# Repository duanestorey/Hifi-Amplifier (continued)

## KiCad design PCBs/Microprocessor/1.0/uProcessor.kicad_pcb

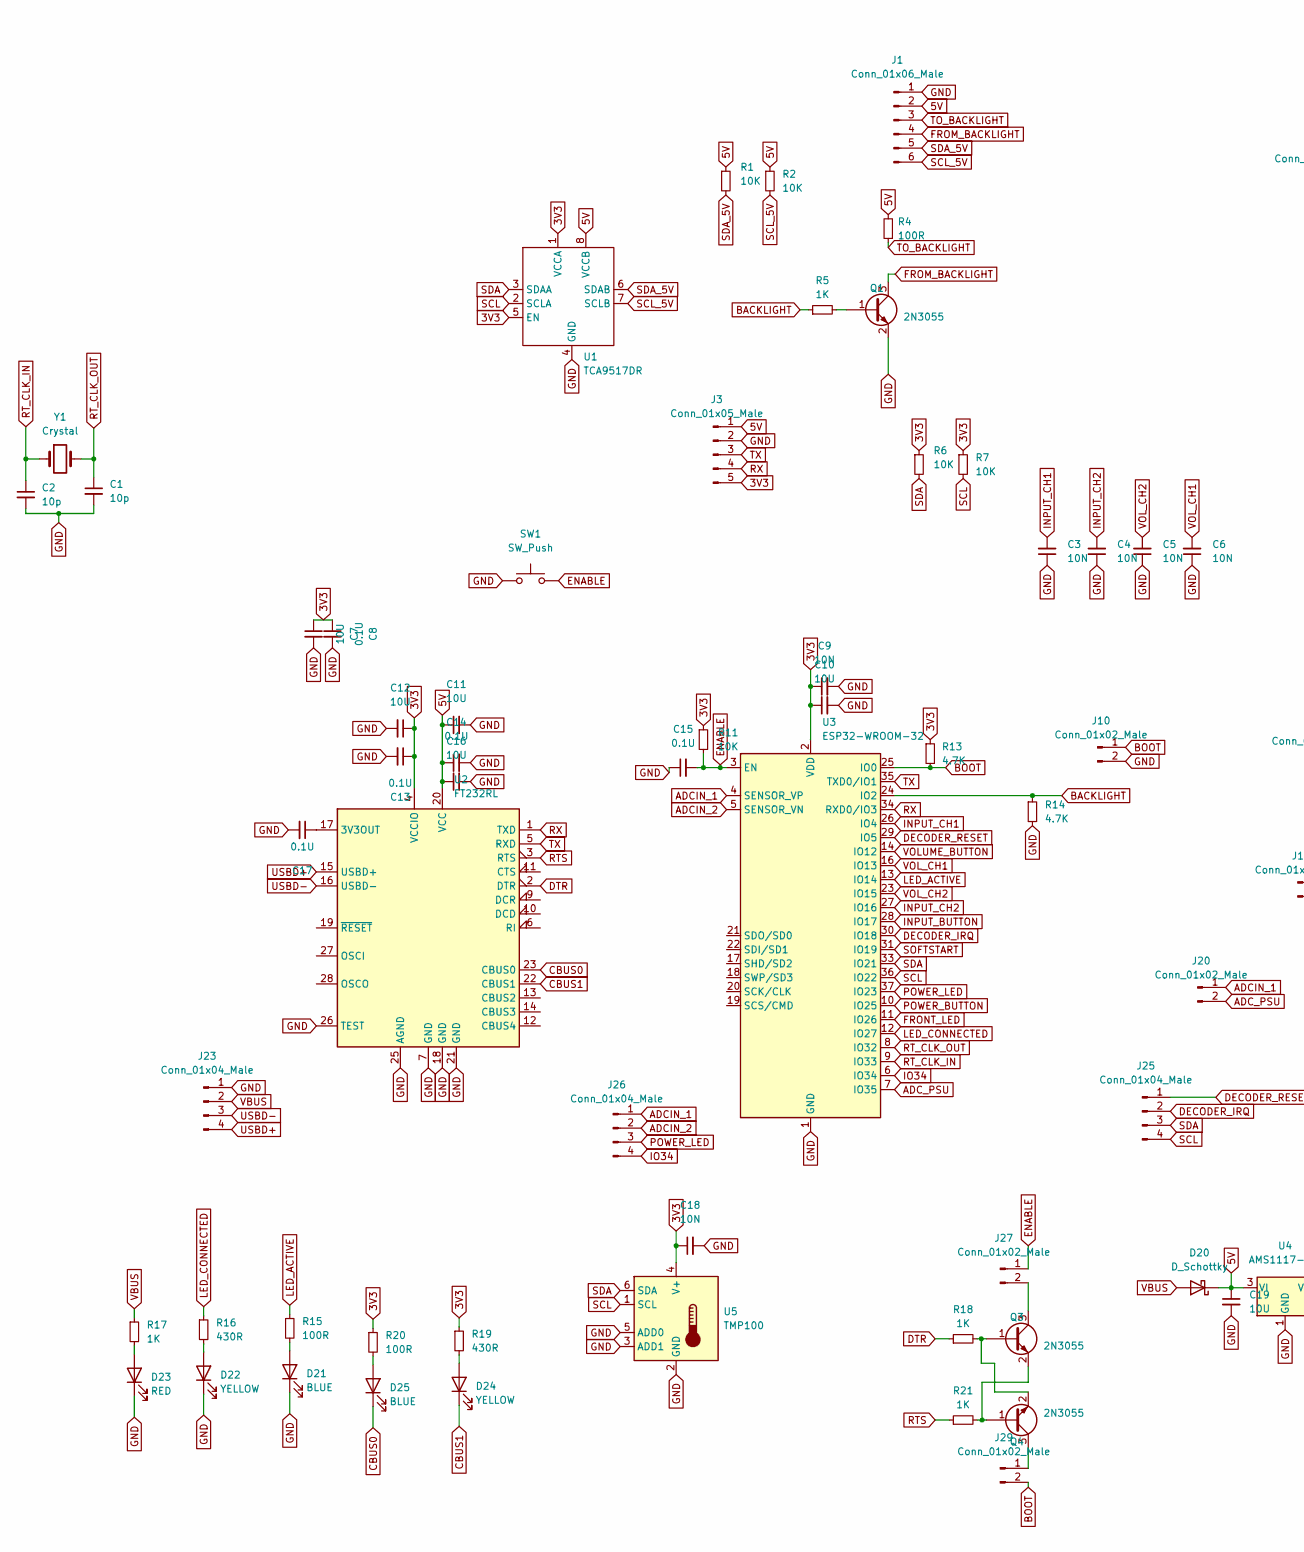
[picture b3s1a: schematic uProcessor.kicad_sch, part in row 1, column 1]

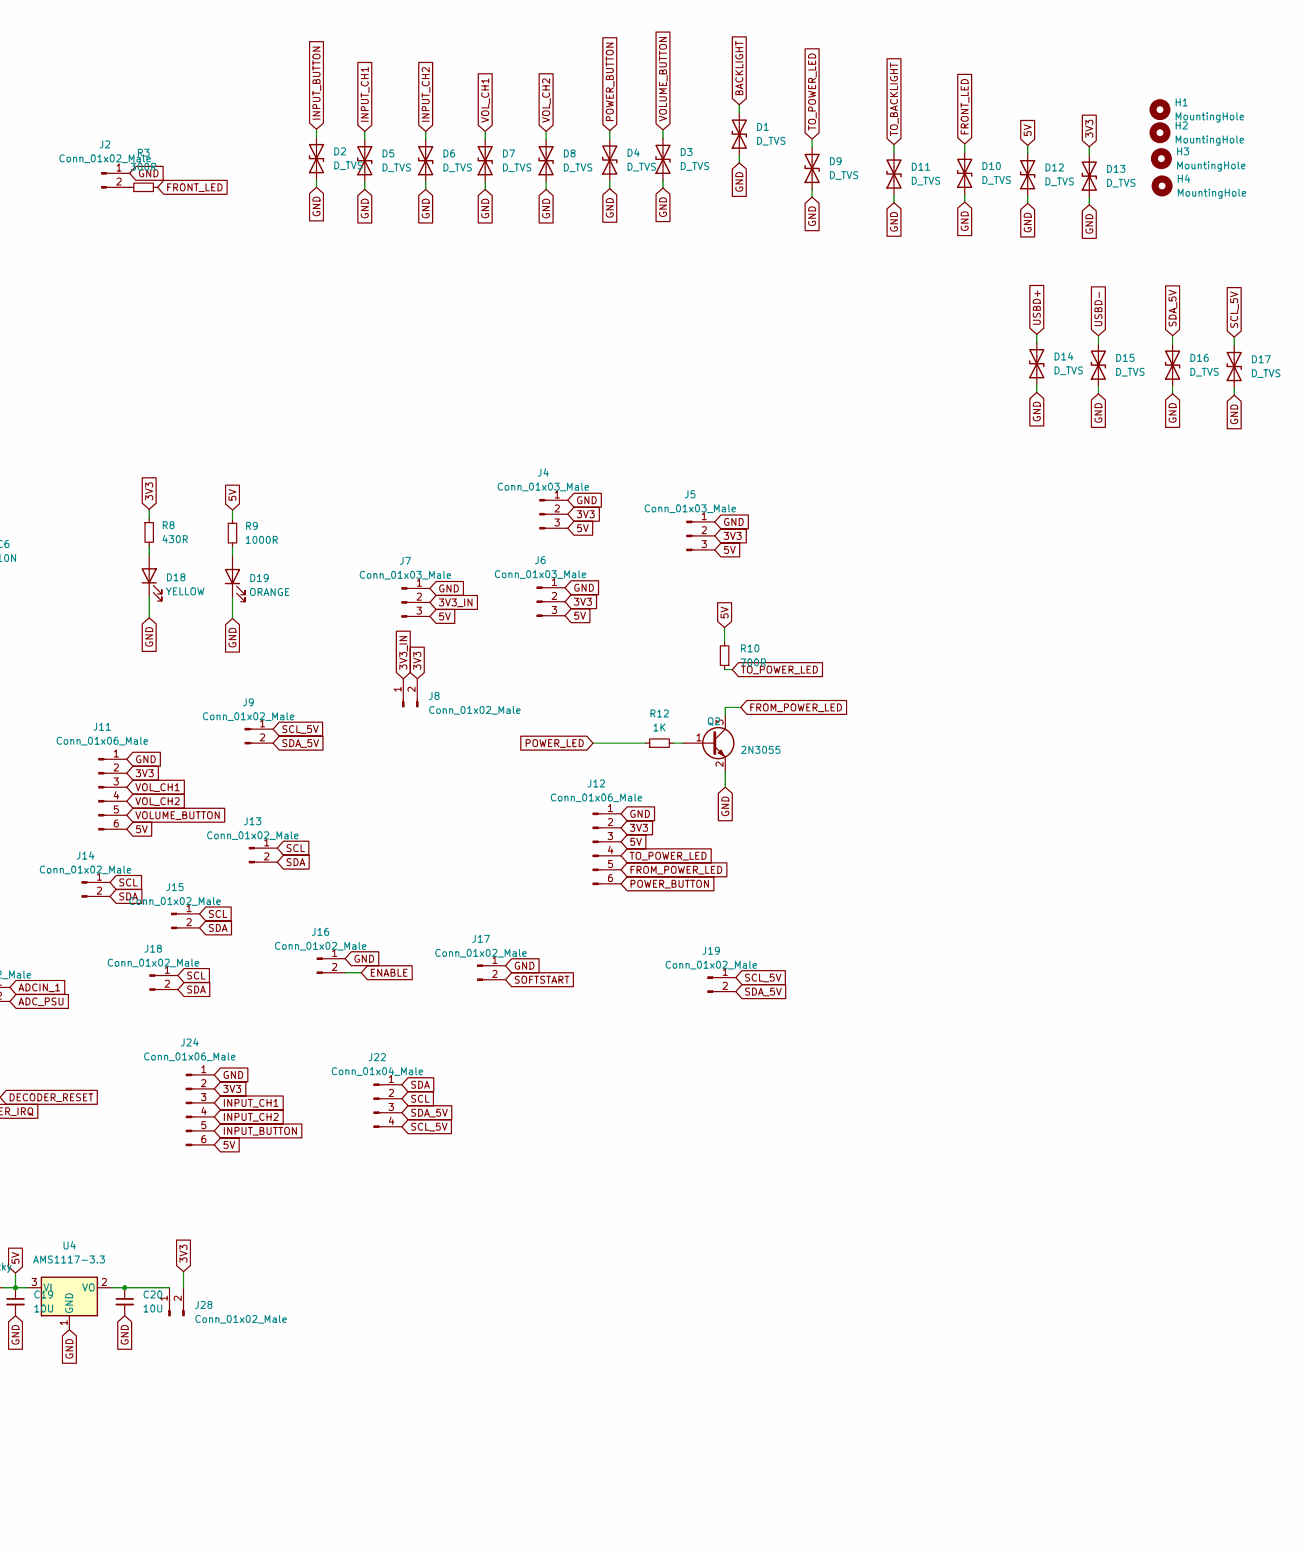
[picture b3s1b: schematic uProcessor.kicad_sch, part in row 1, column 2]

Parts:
C1, C2: 10p; C_0603_1608Metric_Pad1.08x0.95mm_HandSolder
C3, C4, C5, C6: 10N; C_0603_1608Metric_Pad1.08x0.95mm_HandSolder
C7, C10, C11, C12, C16, C19, C20: 10U; C_1206_3216Metric_Pad1.33x1.80mm_HandSolder
C8, C13, C14, C15, C17: 0.1U; C_0805_2012Metric_Pad1.18x1.45mm_HandSolder
C9, C18: 10N; C_0805_2012Metric_Pad1.18x1.45mm_HandSolder
D1, D2, D3, D4, D5, D6, D7, D8, D9, D10, D11, D12, D13, D14, D15, D16, D17: D_TVS; D_SOD-523
D18: YELLOW; LED_0805_2012Metric_Pad1.15x1.40mm_HandSolder; LCSC NCD0603R1
D19: ORANGE; LED_0805_2012Metric_Pad1.15x1.40mm_HandSolder; LCSC XL-1608UBC-04
D20: D_Schottky; D_SMA_Handsoldering
D21, D25: BLUE; LED_0805_2012Metric_Pad1.15x1.40mm_HandSolder; LCSC XL-1608UBC-04
D22, D24: YELLOW; LED_0805_2012Metric_Pad1.15x1.40mm_HandSolder; LCSC XL-1608UBC-04
D23: RED; LED_0805_2012Metric_Pad1.15x1.40mm_HandSolder; LCSC XL-1608UBC-04
H1, H2, H3, H4: MountingHole; MountingHole_3.2mm_M3
J1, J11, J12, J24: Conn_01x06_Male; JST_PH_B6B-PH-K_1x06_P2.00mm_Vertical
J2, J9, J13, J14, J15, J16, J17, J18, J19, J20: Conn_01x02_Male; JST_PH_B2B-PH-K_1x02_P2.00mm_Vertical
J3: Conn_01x05_Male; PinSocket_1x05_P2.54mm_Vertical
J4, J6: Conn_01x03_Male; PinHeader_1x03_P2.54mm_Vertical
J5, J7: Conn_01x03_Male; JST_PH_B3B-PH-K_1x03_P2.00mm_Vertical
J8, J10, J27, J28, J29: Conn_01x02_Male; PinHeader_1x02_P2.54mm_Vertical
J22, J26: Conn_01x04_Male; PinHeader_1x04_P2.54mm_Vertical
J23, J25: Conn_01x04_Male; JST_PH_B4B-PH-K_1x04_P2.00mm_Vertical
Q1, Q2, Q3, Q4: 2N3055; TSOT-23
R1, R2, R6, R7, R11: 10K; R_0603_1608Metric_Pad0.98x0.95mm_HandSolder
R3: 300R; R_0603_1608Metric_Pad0.98x0.95mm_HandSolder
R4, R15, R20: 100R; R_0603_1608Metric_Pad0.98x0.95mm_HandSolder
R5, R12, R17, R18, R21: 1K; R_0603_1608Metric_Pad0.98x0.95mm_HandSolder
R8, R16, R19: 430R; R_0603_1608Metric_Pad0.98x0.95mm_HandSolder
R9: 1000R; R_0603_1608Metric_Pad0.98x0.95mm_HandSolder
R10: 700R; R_0603_1608Metric_Pad0.98x0.95mm_HandSolder
R13, R14: 4.7K; R_0603_1608Metric_Pad0.98x0.95mm_HandSolder
SW1: SW_Push; Button_4x4x1.5
U1: TCA9517DR; SOIC-8_3.9x4.9mm_P1.27mm
U2: FT232RL; SSOP-28_5.3x10.2mm_P0.65mm
U3: ESP32-WROOM-32; ESP32-WROOM-32UE
U4: AMS1117-3.3; SOT-223-3_TabPin2
U5: TMP100; SOT-23-6
Y1: Crystal; Crystal_SMD_EuroQuartz_EQ161-2Pin_3.2x1.5mm_HandSoldering

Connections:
3V3: C7.1, C8.1, C9.1, C10.1, C12.1, C13.1, C18.1, D13.2 (A2), J3.5, J4.2, J5.2, J6.2, J8.2, J11.2, J12.2, J24.2, J28.2, R6.1, R7.1, R8.1, R11.1, R13.1, R19.1, R20.1, U1.1 (VCCA), U1.5 (EN), U2.4 (VCCIO), U3.2 (VDD), U5.4 (V+)
3V3_IN: J7.2, J8.1
5V: C11.1, C14.1, C16.1, C19.1, D12.2 (A2), D20.1 (K), J1.2, J3.1, J4.3, J5.3, J6.3, J7.3, J11.6, J12.3, J24.6, R1.1, R2.1, R4.2, R9.1, R10.2, U1.8 (VCCB), U2.20 (VCC), U4.3 (VI)
ADCIN_1: J20.1, J26.1, U3.4 (SENSOR_VP)
ADCIN_2: J26.2, U3.5 (SENSOR_VN)
ADC_PSU: J20.2, U3.7 (IO35)
BACKLIGHT: D1.2 (A2), R5.1, R14.1, U3.24 (IO2)
BOOT: J10.1, J29.2, R13.2, U3.25 (IO0)
CBUS0: D25.1 (K), U2.23 (CBUS0)
CBUS1: D24.1 (K), U2.22 (CBUS1)
DECODER_IRQ: J25.2, U3.30 (IO18)
DECODER_RESET: J25.1, U3.29 (IO5)
DTR: R18.1, U2.2 (DTR)
ENABLE: C15.2, J16.2, J27.1, R11.2, SW1.2, U3.3 (EN)
FROM_BACKLIGHT: J1.4, Q1.3 (C)
FROM_POWER_LED: J12.5, Q2.3 (C)
FRONT_LED: D10.2 (A2), R3.2, U3.11 (IO26)
GND: C1.2, C2.2, C3.1, C4.1, C5.1, C6.1, C7.2, C8.2, C9.2, C10.2, C11.2, C12.2, C13.2, C14.2, C15.1, C16.2, C17.2, C18.2, C19.2, C20.2, D1.1 (A1), D2.1 (A1), D3.1 (A1), D4.1 (A1), D5.1 (A1), D6.1 (A1), D7.1 (A1), D8.1 (A1), D9.1 (A1), D10.1 (A1), D11.1 (A1), D12.1 (A1), D13.1 (A1), D14.1 (A1), D15.1 (A1), D16.1 (A1), D17.1 (A1), D18.1 (K), D19.1 (K), D21.1 (K), D22.1 (K), D23.1 (K), J1.1, J2.1, J3.2, J4.1, J5.1, J6.1, J7.1, J10.2, J11.1, J12.1, J16.1, J17.1, J23.1, J24.1, Q1.2 (E), Q2.2 (E), R14.2, SW1.1, U1.4 (GND), U2.7 (GND), U2.18 (GND), U2.21 (GND), U2.25 (AGND), U2.26 (TEST), U3.1 (GND), U3.15 (GND), U3.38 (GND), U3.39 (GND), U4.1 (GND), U5.2 (GND), U5.3 (ADD1), U5.5 (ADD0)
INPUT_BUTTON: D2.2 (A2), J24.5, U3.28 (IO17)
INPUT_CH1: C3.2, D5.2 (A2), J24.3, U3.26 (IO4)
INPUT_CH2: C4.2, D6.2 (A2), J24.4, U3.27 (IO16)
IO34: J26.4, U3.6 (IO34)
LED_ACTIVE: R15.1, U3.13 (IO14)
LED_CONNECTED: R16.1, U3.12 (IO27)
unnamed: D18.2 (A), R8.2
unnamed: D19.2 (A), R9.2
unnamed: D21.2 (A), R15.2
unnamed: D22.2 (A), R16.2
unnamed: D23.2 (A), R17.2
unnamed: D24.2 (A), R19.2
unnamed: D25.2 (A), R20.2
unnamed: J2.2, R3.1
unnamed: J27.2, Q3.3 (C)
unnamed: C20.1, J28.1, U4.2 (VO)
unnamed: J29.1, Q4.3 (C)
unnamed: Q1.1 (B), R5.2
unnamed: Q2.1 (B), R12.2
unnamed: Q3.1 (B), Q4.2 (E), R18.2
unnamed: Q3.2 (E), Q4.1 (B), R21.2
unnamed: C17.1, U2.17 (3V3OUT)
POWER_BUTTON: D4.2 (A2), J12.6, U3.10 (IO25)
POWER_LED: J26.3, R12.1, U3.37 (IO23)
RTS: R21.1, U2.3 (RTS)
RT_CLK_IN: C2.1, U3.9 (IO33), Y1.1
RT_CLK_OUT: C1.1, U3.8 (IO32), Y1.2
RX: J3.4, U2.1 (TXD), U3.34 (RXD0/IO3)
SCL: J13.1, J14.1, J15.1, J18.1, J22.2, J25.4, R7.2, U1.2 (SCLA), U3.36 (IO22), U5.1 (SCL)
SCL_5V: D17.2 (A2), J1.6, J9.1, J19.1, J22.4, R2.2, U1.7 (SCLB)
SDA: J13.2, J14.2, J15.2, J18.2, J22.1, J25.3, R6.2, U1.3 (SDAA), U3.33 (IO21), U5.6 (SDA)
SDA_5V: D16.2 (A2), J1.5, J9.2, J19.2, J22.3, R1.2, U1.6 (SDAB)
SOFTSTART: J17.2, U3.31 (IO19)
TO_BACKLIGHT: D11.2 (A2), J1.3, R4.1
TO_POWER_LED: D9.2 (A2), J12.4, R10.1
TX: J3.3, U2.5 (RXD), U3.35 (TXD0/IO1)
USBD+: D14.2 (A2), J23.4, U2.15 (USBD+)
USBD-: D15.2 (A2), J23.3, U2.16 (USBD-)
VBUS: D20.2 (A), J23.2, R17.1
VOLUME_BUTTON: D3.2 (A2), J11.5, U3.14 (IO12)
VOL_CH1: C6.2, D7.2 (A2), J11.3, U3.16 (IO13)
VOL_CH2: C5.2, D8.2 (A2), J11.4, U3.23 (IO15)

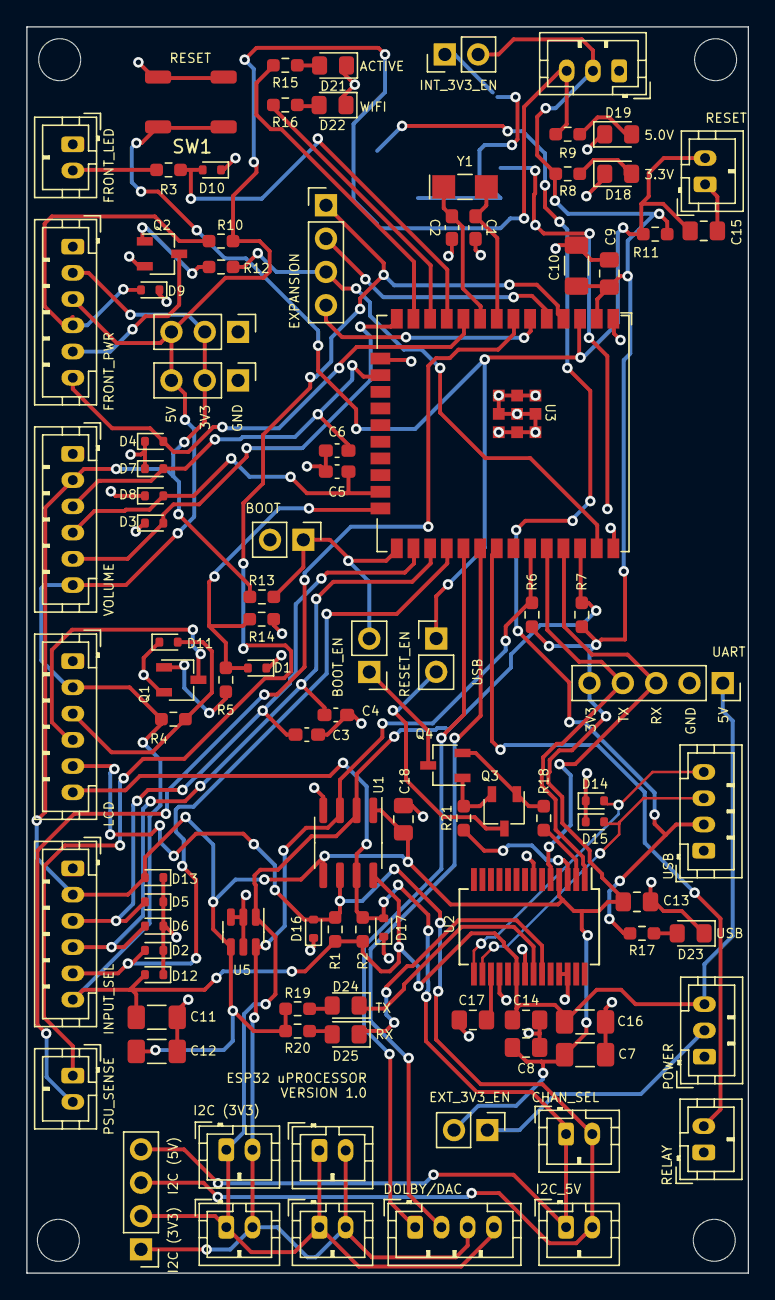
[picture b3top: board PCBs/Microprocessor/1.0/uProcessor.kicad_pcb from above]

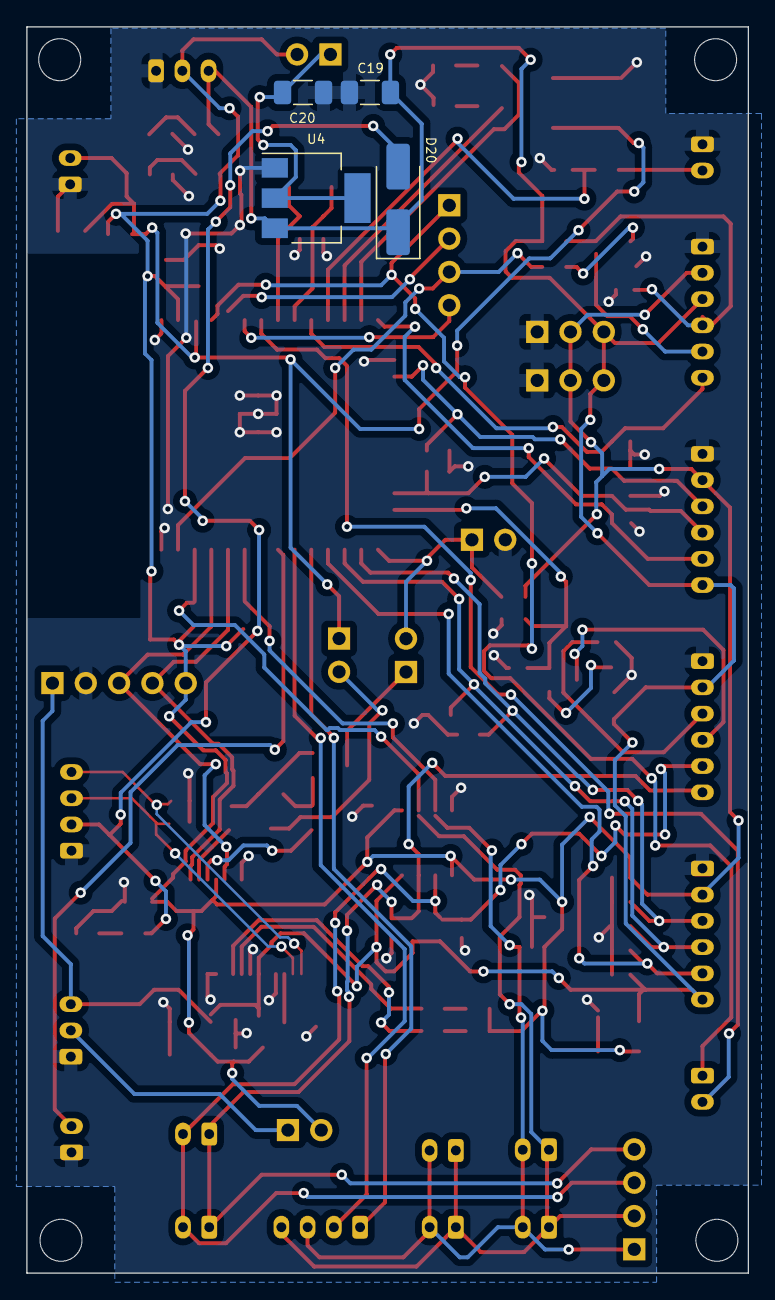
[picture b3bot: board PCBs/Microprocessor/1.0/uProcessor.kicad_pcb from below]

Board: 2 copper layers, 55.0 x 95.0 mm, 109 parts (4 on the bottom side), 60 nets.

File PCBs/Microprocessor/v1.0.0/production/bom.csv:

Designator,Footprint,Quantity,Value,LCSC Part #
"C1, C2",C_0603_1608Metric_Pad1.08x0.95mm_HandSolder,2,10p,
"C10, C11, C12, C16, C19, C20, C7",C_1206_3216Metric_Pad1.33x1.80mm_HandSolder,7,10U,
"C13, C14, C15, C17, C8",C_0805_2012Metric_Pad1.18x1.45mm_HandSolder,5,0.1U,
"C18, C9",C_0805_2012Metric_Pad1.18x1.45mm_HandSolder,2,10N,
"C3, C4, C5, C6",C_0603_1608Metric_Pad1.08x0.95mm_HandSolder,4,10N,
"D1, D10, D11, D12, D13, D14, D15, D16, D17, D2, D3, D4, D5, D6, D7, D8, D9",D_SOD-523,17,D_TVS,
"D18, D22, D24",LED_0805_2012Metric_Pad1.15x1.40mm_HandSolder,3,YELLOW,NCD0603R1
D19,LED_0805_2012Metric_Pad1.15x1.40mm_HandSolder,1,ORANGE,XL-1608UBC-04
D20,D_SMA_Handsoldering,1,D_Schottky,
"D21, D25",LED_0805_2012Metric_Pad1.15x1.40mm_HandSolder,2,BLUE,XL-1608UBC-04
D23,LED_0805_2012Metric_Pad1.15x1.40mm_HandSolder,1,RED,XL-1608UBC-04
"H1, H2, H3, H4",MountingHole_3.2mm_M3,4,MountingHole,
"J1, J11, J12, J24",JST_PH_B6B-PH-K_1x06_P2.00mm_Vertical,4,Conn_01x06_Male,
"J10, J27, J28, J29, J8",PinHeader_1x02_P2.54mm_Vertical,5,Conn_01x02_Male,
"J13, J14, J15, J16, J17, J18, J19, J2, J20, J9",JST_PH_B2B-PH-K_1x02_P2.00mm_Vertical,10,Conn_01x02_Male,
"J22, J26",PinHeader_1x04_P2.54mm_Vertical,2,Conn_01x04_Male,
"J23, J25",JST_PH_B4B-PH-K_1x04_P2.00mm_Vertical,2,Conn_01x04_Male,
J3,PinSocket_1x05_P2.54mm_Vertical,1,Conn_01x05_Male,
"J4, J6",PinHeader_1x03_P2.54mm_Vertical,2,Conn_01x03_Male,
"J5, J7",JST_PH_B3B-PH-K_1x03_P2.00mm_Vertical,2,Conn_01x03_Male,
"Q1, Q2, Q3, Q4",TSOT-23,4,2N3055,
"R1, R11, R2, R6, R7",R_0603_1608Metric_Pad0.98x0.95mm_HandSolder,5,10K,
R10,R_0603_1608Metric_Pad0.98x0.95mm_HandSolder,1,700R,
"R12, R17, R18, R21, R5",R_0603_1608Metric_Pad0.98x0.95mm_HandSolder,5,1K,
"R13, R14",R_0603_1608Metric_Pad0.98x0.95mm_HandSolder,2,4.7K,
"R15, R20, R4",R_0603_1608Metric_Pad0.98x0.95mm_HandSolder,3,100R,
"R16, R19, R8",R_0603_1608Metric_Pad0.98x0.95mm_HandSolder,3,430R,
R3,R_0603_1608Metric_Pad0.98x0.95mm_HandSolder,1,300R,
R9,R_0603_1608Metric_Pad0.98x0.95mm_HandSolder,1,1000R,
SW1,Button_4x4x1.5,1,SW_Push,
U1,SOIC-8_3.9x4.9mm_P1.27mm,1,TCA9517DR,
U2,SSOP-28_5.3x10.2mm_P0.65mm,1,FT232RL,
U3,ESP32-WROOM-32UE,1,ESP32-WROOM-32,
U4,SOT-223-3_TabPin2,1,AMS1117-3.3,
U5,SOT-23-6,1,TMP100,
Y1,Crystal_SMD_EuroQuartz_EQ161-2Pin_3.2x1.5mm_HandSoldering,1,Crystal,

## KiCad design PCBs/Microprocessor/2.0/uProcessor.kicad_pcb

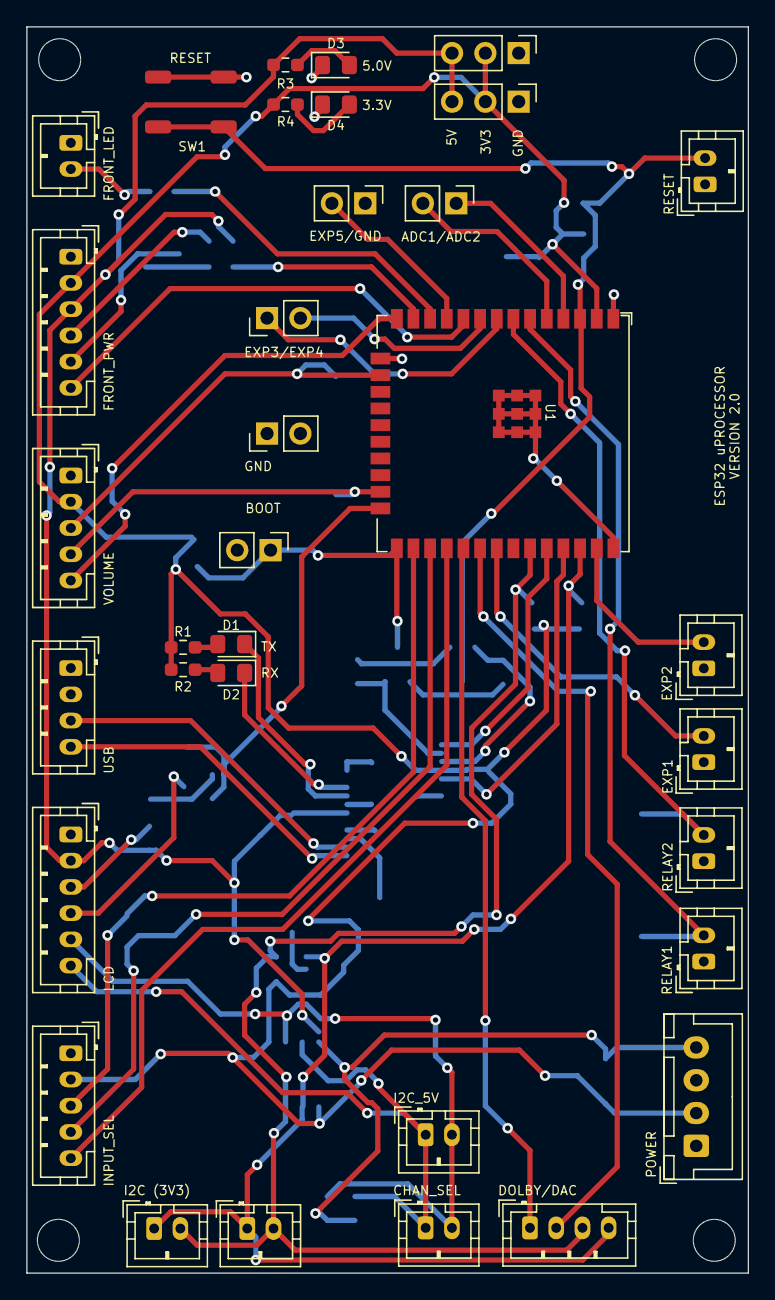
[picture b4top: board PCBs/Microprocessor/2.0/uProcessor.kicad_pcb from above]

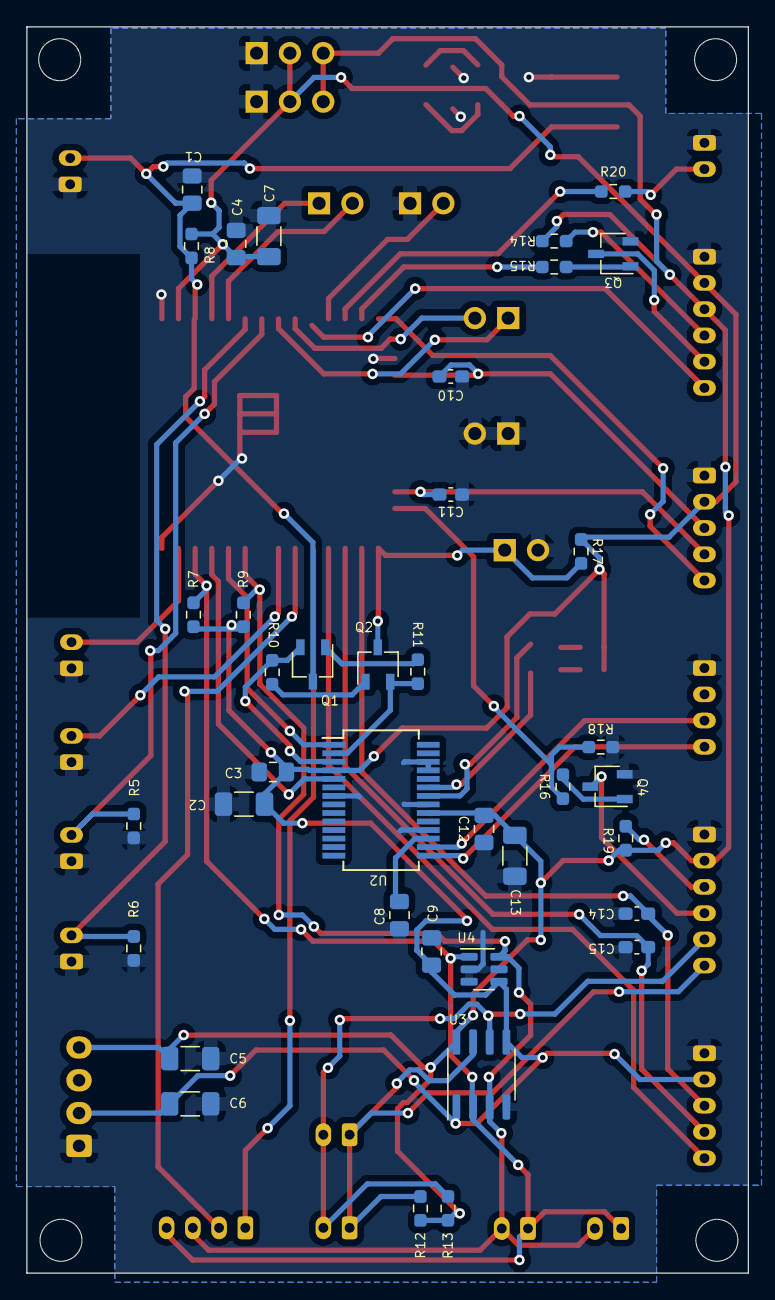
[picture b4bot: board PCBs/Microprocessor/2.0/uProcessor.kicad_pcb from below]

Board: 2 copper layers, 55.0 x 95.0 mm, 76 parts (38 on the bottom side), 52 nets.

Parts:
C1, C3, C8, C12: 0.1U; C_0805_2012Metric_Pad1.18x1.45mm_HandSolder
C2, C5, C6, C7, C13: 10U; C_1206_3216Metric_Pad1.33x1.80mm_HandSolder
C4: 10N; C_0805_2012Metric_Pad1.18x1.45mm_HandSolder
C9: 100n; C_0805_2012Metric_Pad1.18x1.45mm_HandSolder
C10, C11, C14, C15: 10N; C_0603_1608Metric_Pad1.08x0.95mm_HandSolder
D1, D4: YELLOW; LED_0805_2012Metric_Pad1.15x1.40mm_HandSolder
D2: BLUE; LED_0805_2012Metric_Pad1.15x1.40mm_HandSolder
D3: ORANGE; LED_0805_2012Metric_Pad1.15x1.40mm_HandSolder
H1, H2, H3, H4: MountingHole; MountingHole_3.2mm_M3
J1, J7, J10, J13, J14, J20, J21, J22, J23, J24: Conn_01x02_Male; JST_PH_B2B-PH-K_1x02_P2.00mm_Vertical
J2, J5: Conn_01x06_Male; JST_PH_B6B-PH-K_1x06_P2.00mm_Vertical
J3, J6: Conn_01x05_Pin; JST_PH_B5B-PH-K_1x05_P2.00mm_Vertical
J4, J18: Conn_01x04_Male; JST_PH_B4B-PH-K_1x04_P2.00mm_Vertical
J8, J9, J11, J12, J15: Conn_01x02_Male; PinHeader_1x02_P2.54mm_Vertical
J16, J17: Conn_01x03_Male; PinHeader_1x03_P2.54mm_Vertical
J19: Conn_01x04_Pin; JST_XH_B4B-XH-A_1x04_P2.50mm_Vertical
Q1, Q2, Q3, Q4: 2N3055; TSOT-23
R1, R4: 430R; R_0603_1608Metric_Pad0.98x0.95mm_HandSolder
R2, R19: 100R; R_0603_1608Metric_Pad0.98x0.95mm_HandSolder
R3: 1000R; R_0603_1608Metric_Pad0.98x0.95mm_HandSolder
R5, R6: 4K7; R_0603_1608Metric_Pad0.98x0.95mm_HandSolder
R7, R9, R10, R11, R12, R13: 10K; R_0603_1608Metric_Pad0.98x0.95mm_HandSolder
R8, R17, R18: 4.7K; R_0603_1608Metric_Pad0.98x0.95mm_HandSolder
R14: 700R; R_0603_1608Metric_Pad0.98x0.95mm_HandSolder
R15, R16: 1K; R_0603_1608Metric_Pad0.98x0.95mm_HandSolder
R20: 300R; R_0603_1608Metric_Pad0.98x0.95mm_HandSolder
SW1: SW_Push; Button Aliexpress 4x4
U1: ESP32-WROOM-32; ESP32-WROOM-32UE
U2: FT232RL; SSOP-28_5.3x10.2mm_P0.65mm
U3: TCA9517DR; SOIC-8_3.9x4.9mm_P1.27mm
U4: TMP100; SOT-23-6

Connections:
3V3: C2.1, C3.1, C4.1, C6.1, C7.1, C9.1, J2.2, J3.2, J6.2, J16.2, J17.2, J19.2, R1.1, R2.1, R4.1, R7.1, R8.1, R9.1, R17.1, U1.2 (VDD), U2.4 (VCCIO), U3.1 (VCCA), U3.5 (EN), U4.4 (V+)
5V: C5.1, C12.1, C13.1, J2.3, J5.2, J16.3, J17.3, J19.4, R3.1, R12.1, R13.1, R14.2, R19.2, U2.20 (VCC), U3.8 (VCCB)
ADC1: J15.1, U1.4 (SENSOR_VP)
ADC2: J15.2, U1.5 (SENSOR_VN)
BACKLIGHT: R16.1, R18.1, U1.24 (IO2)
BOOT: J11.1, Q2.3 (C), R17.2, U1.25 (IO0)
CBUS0: D2.1 (K), U2.23 (CBUS0)
CBUS1: D1.1 (K), U2.22 (CBUS1)
DECODER_IRQ: J18.2, U1.30 (IO18)
DECODER_RESET: J18.1, U1.29 (IO5)
DTR: Q2.2 (E), R11.1, U2.2 (DTR)
ENABLE: C1.2, J23.2, Q1.3 (C), R8.2, SW1.2, U1.3 (EN)
EXP1: J21.2, U1.31 (IO19)
EXP2: J20.2, U1.37 (IO23)
EXP3: J8.1, U1.8 (IO32)
EXP4: J8.2, U1.9 (IO33)
EXP5: J12.2, U1.11 (IO26)
FROM_BACKLIGHT: J5.4, Q4.3 (C)
FROM_POWER_LED: J2.5, Q3.3 (C)
FRONT_LED: R20.2, U1.12 (IO27)
GND: C1.1, C2.2, C3.2, C4.2, C5.2, C6.2, C7.2, C8.2, C9.2, C10.1, C11.1, C12.2, C13.2, C14.1, C15.1, D3.1 (K), D4.1 (K), J1.1, J2.1, J3.1, J4.1, J5.1, J6.1, J9.1, J9.2, J11.2, J12.1, J16.1, J17.1, J19.1, J20.1, J21.1, J22.1, J23.1, J24.1, Q3.2 (E), Q4.2 (E), R5.1, R6.1, R18.2, SW1.1, U1.1 (GND), U1.15 (GND), U1.38 (GND), U1.39 (GND), U2.7 (GND), U2.18 (GND), U2.21 (GND), U2.25 (AGND), U2.26 (TEST), U3.4 (GND), U4.2 (GND), U4.3 (ADD1), U4.5 (ADD0)
INPUT_BUTTON: J6.5, U1.28 (IO17)
INPUT_CH1: C14.2, J6.3, U1.26 (IO4)
INPUT_CH2: C15.2, J6.4, U1.27 (IO16)
unnamed: D1.2 (A), R1.2
unnamed: D2.2 (A), R2.2
unnamed: D3.2 (A), R3.2
unnamed: D4.2 (A), R4.2
unnamed: J1.2, R20.1
unnamed: Q1.1 (B), R11.2
unnamed: Q2.1 (B), R10.2
unnamed: Q3.1 (B), R15.2
unnamed: Q4.1 (B), R16.2
unnamed: C8.1, U2.17 (3V3OUT)
POWER_BUTTON: J2.6, U1.10 (IO25)
POWER_LED: R15.1, U1.13 (IO14)
RELAY1: J24.2, R6.2, U1.6 (IO34)
RELAY2: J22.2, R5.2, U1.7 (IO35)
RTS: Q1.2 (E), R10.1, U2.3 (RTS)
RX: U1.34 (RXD0/IO3), U2.1 (TXD)
SCL: J7.1, J10.1, J18.4, R7.2, U1.36 (IO22), U3.2 (SCLA), U4.1 (SCL)
SCL_5V: J5.6, J13.1, J14.1, R12.2, U3.7 (SCLB)
SDA: J7.2, J10.2, J18.3, R9.2, U1.33 (IO21), U3.3 (SDAA), U4.6 (SDA)
SDA_5V: J5.5, J13.2, J14.2, R13.2, U3.6 (SDAB)
TO_BACKLIGHT: J5.3, R19.1
TO_POWER_LED: J2.4, R14.1
TX: U1.35 (TXD0/IO1), U2.5 (RXD)
USBD+: J4.4, U2.15 (USBD+)
USBD-: J4.3, U2.16 (USBD-)
VOLUME_BUTTON: J3.5, U1.14 (IO12)
VOL_CH1: C10.2, J3.3, U1.16 (IO13)
VOL_CH2: C11.2, J3.4, U1.23 (IO15)

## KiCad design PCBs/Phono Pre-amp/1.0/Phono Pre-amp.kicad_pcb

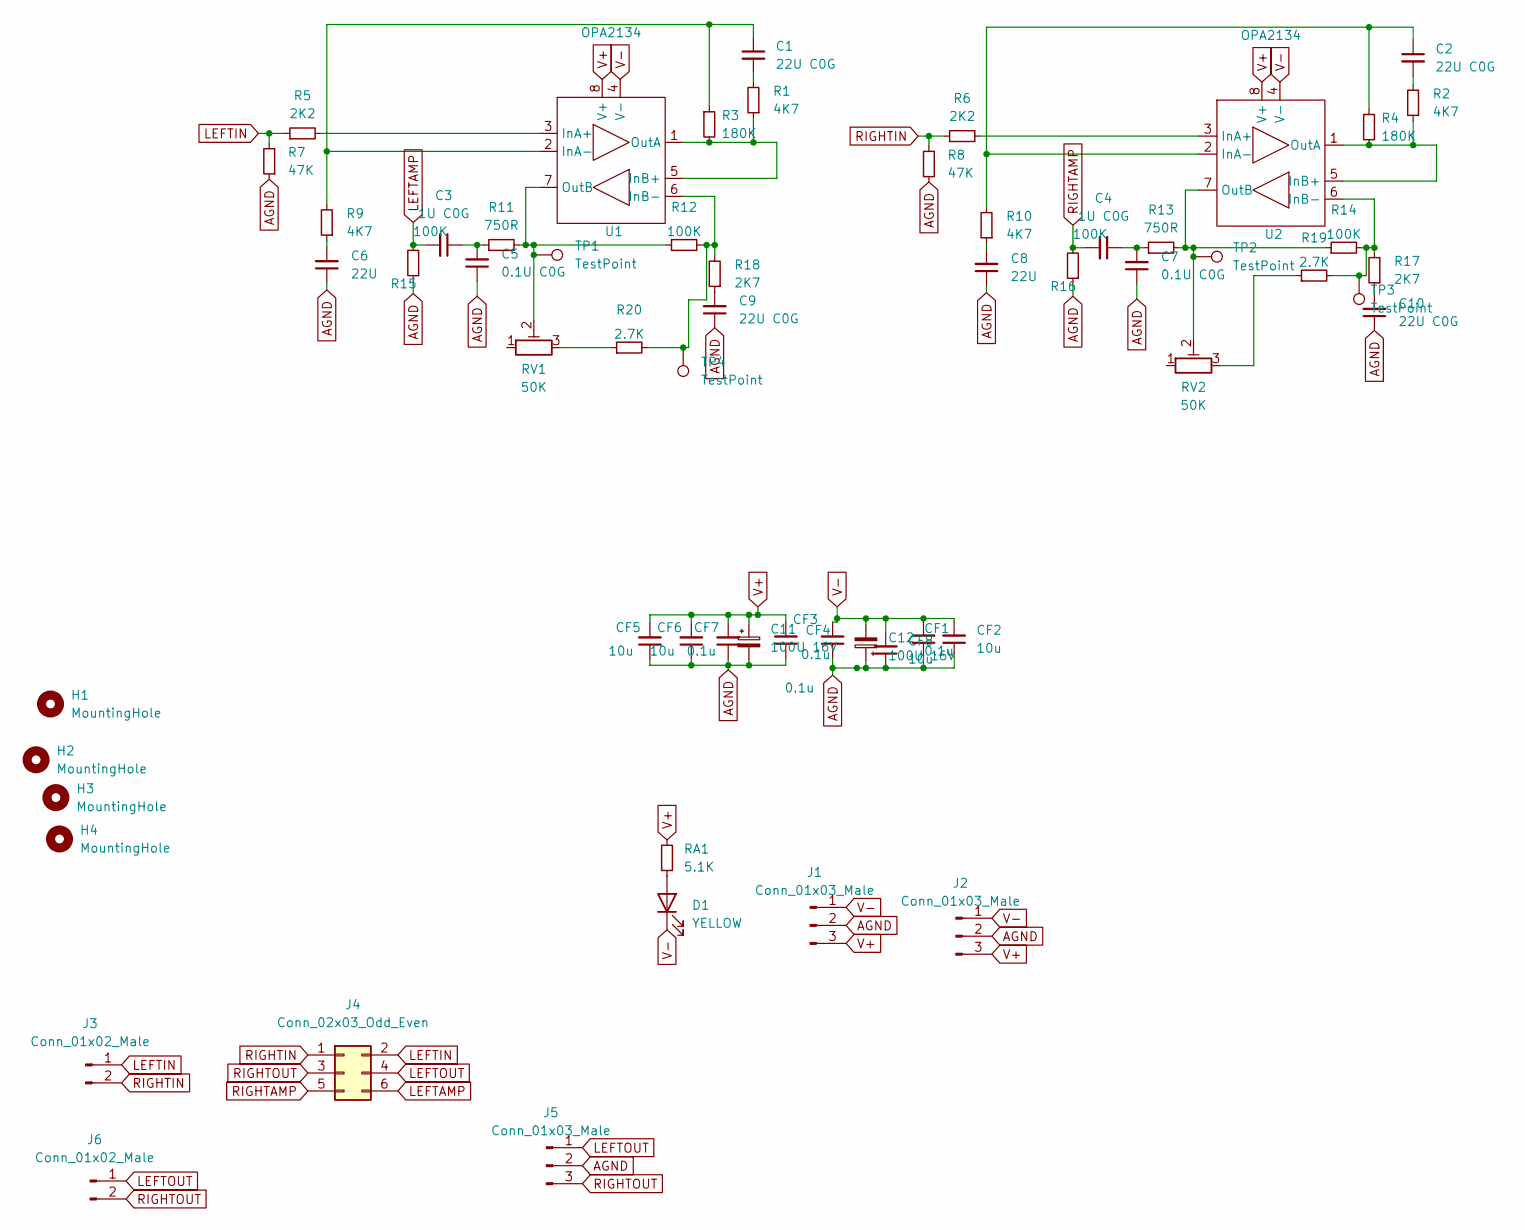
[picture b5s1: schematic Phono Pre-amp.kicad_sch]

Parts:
C1, C2, C9, C10: 22U C0G; CP_Radial_D5.0mm_P2.00mm
C3, C4: 1U C0G; CP_Radial_D5.0mm_P2.00mm
C5, C7: 0.1U C0G; C_1206_3216Metric_Pad1.33x1.80mm_HandSolder
C6, C8: 22U; CP_Radial_D5.0mm_P2.00mm
C11, C12: 100U 16V; CP_Radial_D6.3mm_P2.50mm
CF1, CF3, CF4, CF7: 0.1u; C_0805_2012Metric_Pad1.18x1.45mm_HandSolder
CF2, CF5, CF6, CF8: 10u; C_1206_3216Metric_Pad1.33x1.80mm_HandSolder
D1: YELLOW; LED_0805_2012Metric_Pad1.15x1.40mm_HandSolder
H1, H2, H3, H4: MountingHole; MountingHole_3.2mm_M3
J1, J2: Conn_01x03_Male; JST_PH_B3B-PH-K_1x03_P2.00mm_Vertical
J3, J6: Conn_01x02_Male; JST_PH_B2B-PH-K_1x02_P2.00mm_Vertical
J4: Conn_02x03_Odd_Even; PinHeader_2x03_P2.54mm_Vertical
J5: Conn_01x03_Male; PinHeader_1x03_P2.54mm_Vertical
R1, R2, R9, R10: 4K7; R_0805_2012Metric_Pad1.20x1.40mm_HandSolder
R3, R4: 180K; R_0805_2012Metric_Pad1.20x1.40mm_HandSolder
R5, R6: 2K2; R_0805_2012Metric_Pad1.20x1.40mm_HandSolder
R7, R8: 47K; R_0805_2012Metric_Pad1.20x1.40mm_HandSolder
R11, R13: 750R; R_0805_2012Metric_Pad1.20x1.40mm_HandSolder
R12, R14, R15, R16: 100K; R_0805_2012Metric_Pad1.20x1.40mm_HandSolder
R17, R18: 2K7; R_0805_2012Metric_Pad1.20x1.40mm_HandSolder
R19, R20: 2.7K; R_0805_2012Metric_Pad1.20x1.40mm_HandSolder
RA1: 5.1K; R_0603_1608Metric
RV1, RV2: 50K; Potentiometer_Bourns_3296W_Vertical
TP1, TP2, TP3, TP4: TestPoint; TestPoint_THTPad_1.5x1.5mm_Drill0.7mm
U1, U2: OPA2134; DIP-8_W7.62mm_Socket

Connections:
AGND: C5.1, C6.1, C7.1, C8.1, C9.1, C10.1, C11.2, C12.1, CF1.1, CF2.1, CF3.1, CF4.1, CF5.1, CF6.1, CF7.1, CF8.1, J1.2, J2.2, J5.2, R7.1, R8.1, R15.1, R16.1
LEFTAMP: C3.2, J4.6, R15.2
LEFTIN: J3.1, J4.2, R5.1, R7.2
LEFTOUT: J4.4, J5.1, J6.1
unnamed: C1.1, R3.1, R9.2, U1.2 (InA-)
unnamed: C1.2, R1.2
unnamed: C2.1, R4.1, R10.2, U2.2 (InA-)
unnamed: C2.2, R2.2
unnamed: C3.1, C5.2, R11.1
unnamed: C4.1, C7.2, R13.1
unnamed: C6.2, R9.1
unnamed: C8.2, R10.1
unnamed: C9.2, R18.1
unnamed: C10.2, R17.1
unnamed: D1.2 (A), RA1.1
unnamed: R1.1, R3.2, U1.1 (OutA), U1.5 (InB+)
unnamed: R2.1, R4.2, U2.1 (OutA), U2.5 (InB+)
unnamed: R5.2, U1.3 (InA+)
unnamed: R6.2, U2.3 (InA+)
unnamed: R11.2, R12.1, RV1.2, TP1.1, U1.7 (OutB)
unnamed: R12.2, R18.2, R20.2, TP4.1, U1.6 (InB-)
unnamed: R13.2, R14.1, RV2.2, TP2.1, U2.7 (OutB)
unnamed: R14.2, R17.2, R19.2, TP3.1, U2.6 (InB-)
unnamed: R20.1, RV1.3
unnamed: R19.1, RV2.3
RIGHTAMP: C4.2, J4.5, R16.2
RIGHTIN: J3.2, J4.1, R6.1, R8.2
RIGHTOUT: J4.3, J5.3, J6.2
V+: C11.1, CF3.2, CF5.2, CF6.2, CF7.2, J1.3, J2.3, RA1.2, U1.8 (V+), U2.8 (V+)
V-: C12.2, CF1.2, CF2.2, CF4.2, CF8.2, D1.1 (K), J1.1, J2.1, U1.4 (V-), U2.4 (V-)

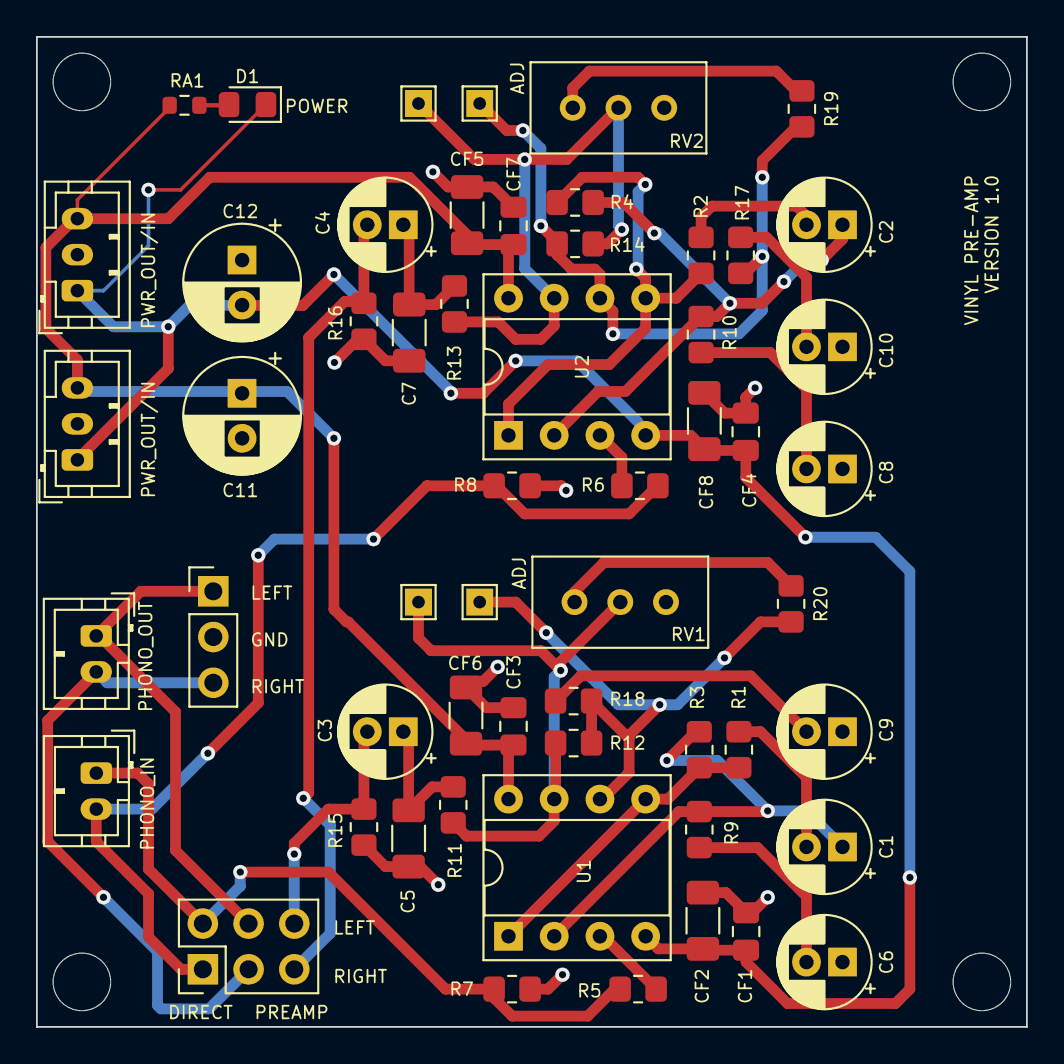
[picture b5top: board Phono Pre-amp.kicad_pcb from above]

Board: 2 copper layers, 55.0 x 55.0 mm, 60 parts (0 on the bottom side), 30 nets.
